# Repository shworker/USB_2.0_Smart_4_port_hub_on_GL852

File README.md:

# USB 2.0 Smart 4 port hub based on GL852
Not tested.
KiCAD 6 project + Screenshot with 3D View of PCB

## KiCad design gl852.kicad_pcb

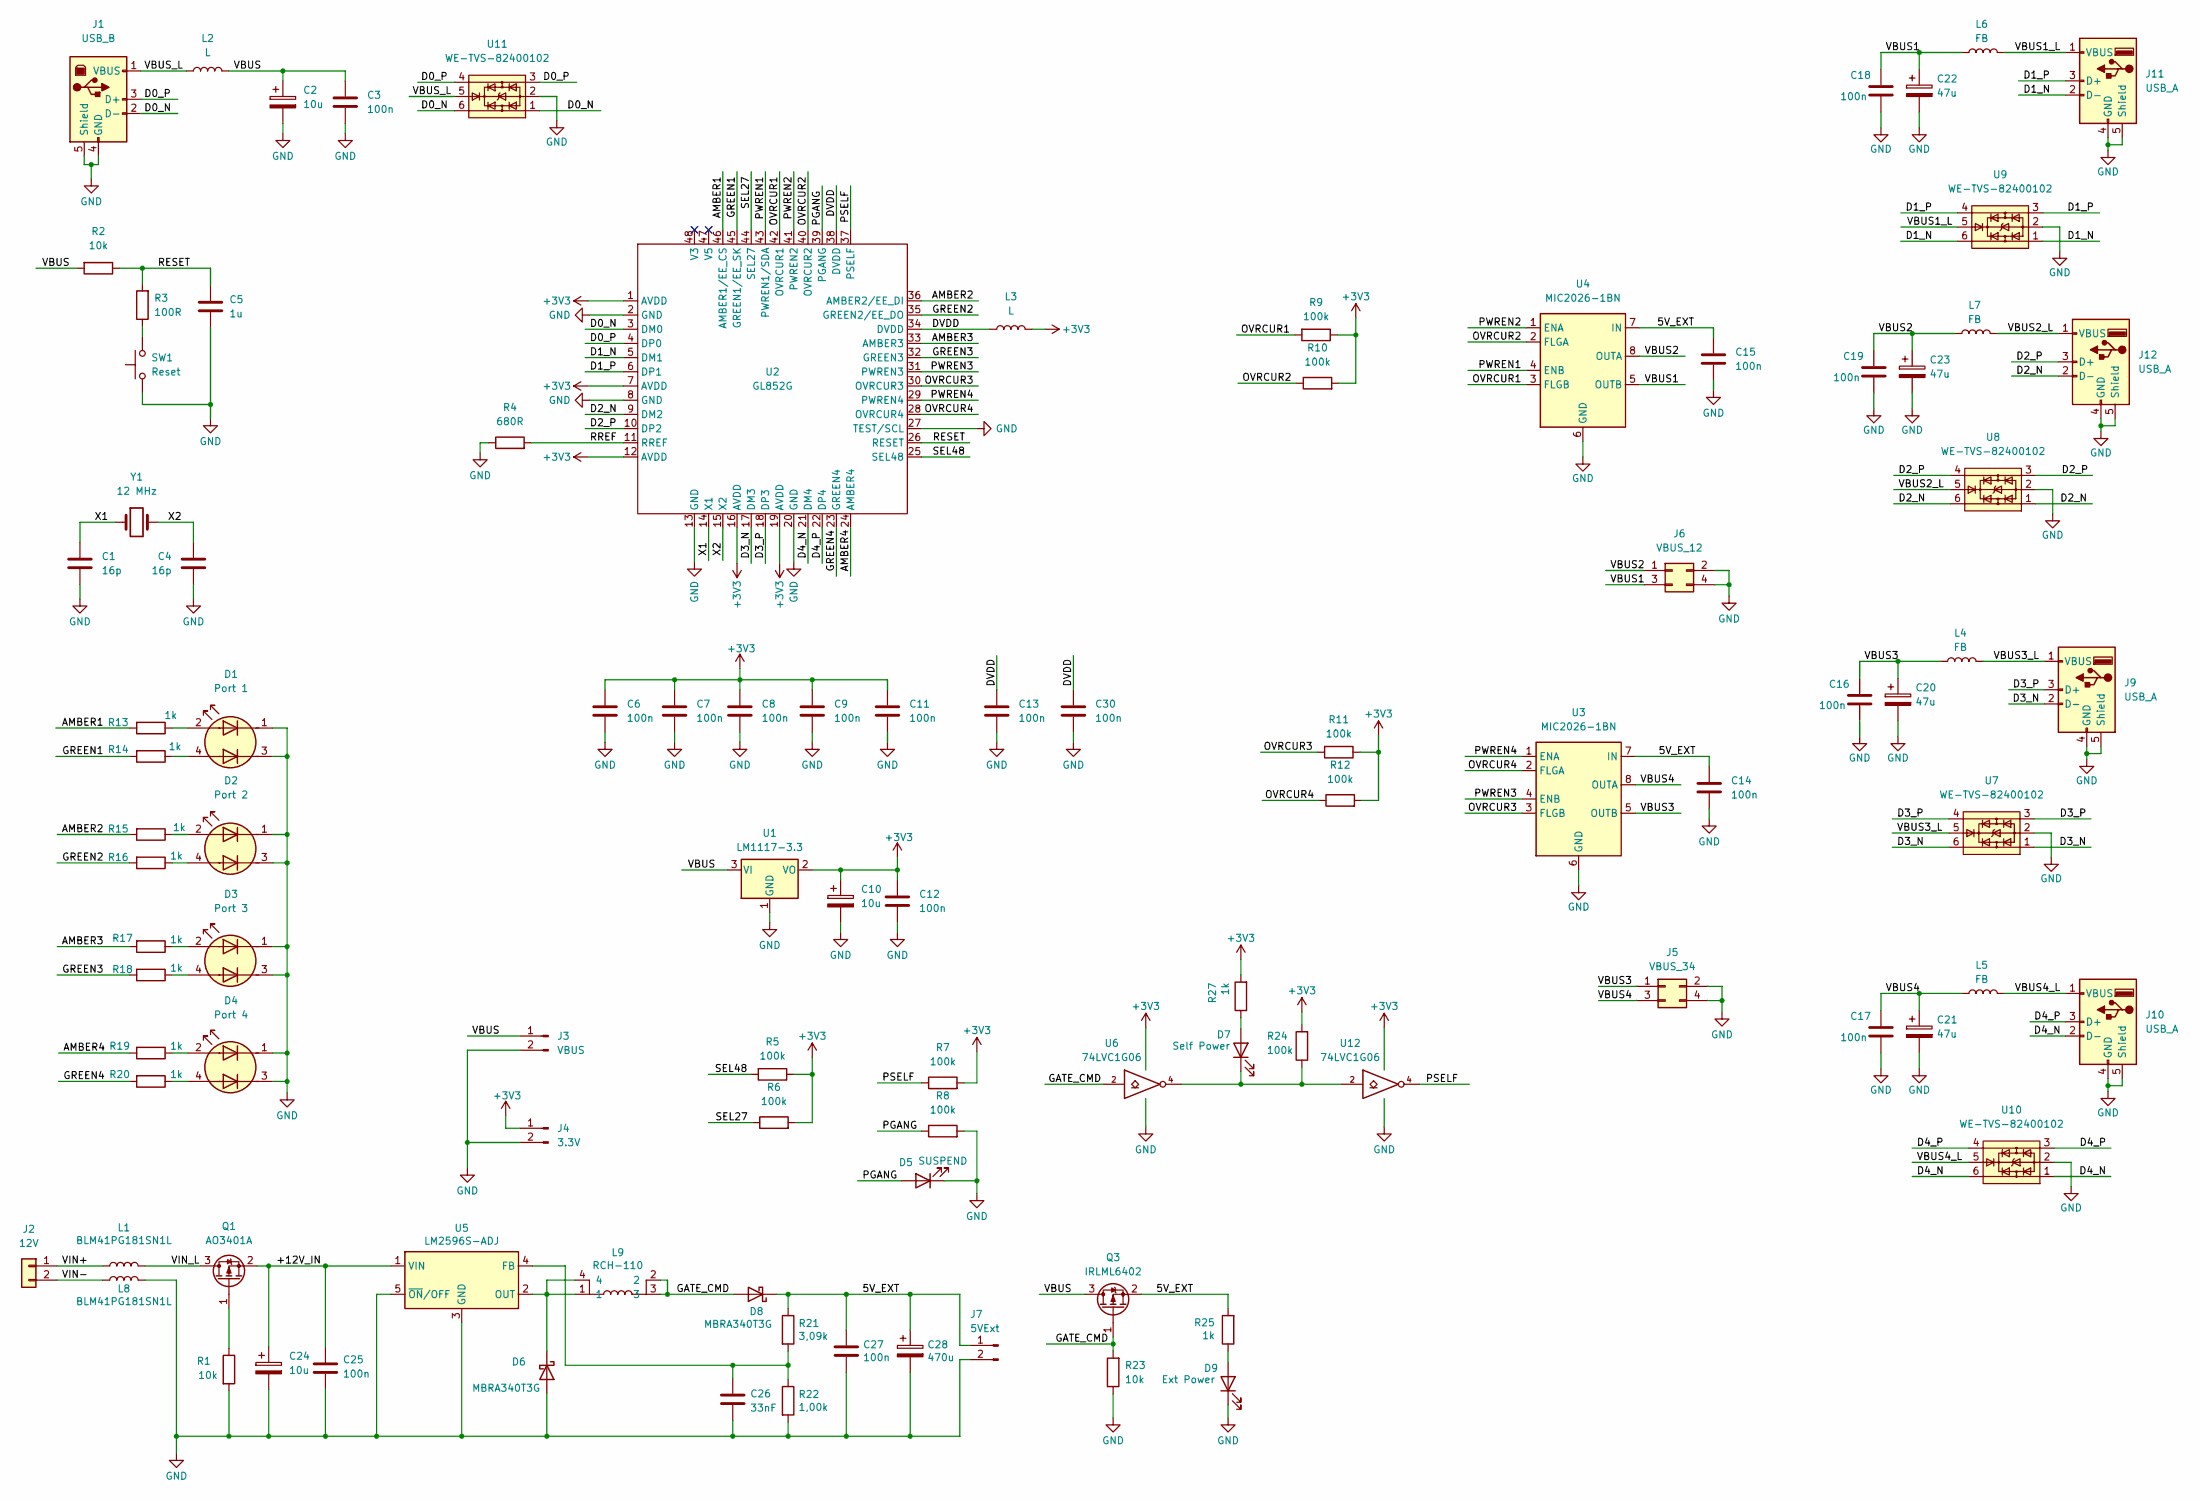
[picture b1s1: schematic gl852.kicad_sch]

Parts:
C1, C4: 16p; C_0603_1608Metric_Pad1.08x0.95mm_HandSolder
C2: 10u; CP_EIA-3528-21_Kemet-B_Pad1.50x2.35mm_HandSolder
C3, C6, C7, C8, C9, C11, C12, C13, C14, C15, C16, C17, C18, C19, C25, C27, C30: 100n; C_0603_1608Metric_Pad1.08x0.95mm_HandSolder
C5: 1u; C_0603_1608Metric_Pad1.08x0.95mm_HandSolder
C10: 10u; CP_Radial_D5.0mm_P2.50mm
C20, C21, C22, C23: 47u; C_Radial_D6.3mm_H5.0mm_P2.50mm
C24: 10u; CP_Radial_D10.0mm_P5.00mm
C26: 33nF; C_0603_1608Metric_Pad1.08x0.95mm_HandSolder
C28: 470u; CP_Radial_D8.0mm_P3.50mm
D1: Port 1; LED_Kingbright_AAA3528ESGCT
D2: Port 2; LED_Kingbright_AAA3528ESGCT
D3: Port 3; LED_Kingbright_AAA3528ESGCT
D4: Port 4; LED_Kingbright_AAA3528ESGCT
D5: SUSPEND; LED_0805_2012Metric_Pad1.15x1.40mm_HandSolder
D6, D8: MBRA340T3G; D_SMC_Handsoldering
D7: Self Power; LED_0805_2012Metric_Pad1.15x1.40mm_HandSolder
D9: Ext Power; LED_0805_2012Metric_Pad1.15x1.40mm_HandSolder
J1: USB_B; USB_B_OST_USB-B1HSxx_Horizontal
J2: 12V; PinHeader_1x02_P2.54mm_Vertical
J3: VBUS; PinHeader_1x02_P2.54mm_Vertical
J4: 3.3V; PinHeader_1x02_P2.54mm_Vertical
J5: VBUS_34; PinHeader_2x02_P2.54mm_Vertical
J6: VBUS_12; PinHeader_2x02_P2.54mm_Vertical
J7: 5VExt; PinHeader_1x02_P2.54mm_Vertical
J9, J10, J11, J12: USB_A; USB_A_CONNFLY_DS1095-WNR0
L1, L8: BLM41PG181SN1L; L_1806_4516Metric_Pad1.45x1.90mm_HandSolder
L2, L3: L; L_0805_2012Metric_Pad1.15x1.40mm_HandSolder
L4, L5, L6, L7: FB; L_0603_1608Metric_Pad1.05x0.95mm_HandSolder
L9: RCH-110; RCH110
Q1: AO3401A; SOT-23_Handsoldering
Q3: IRLML6402; SOT-23_Handsoldering
R1, R2, R23: 10k; R_0603_1608Metric_Pad0.98x0.95mm_HandSolder
R3: 100R; R_0603_1608Metric_Pad0.98x0.95mm_HandSolder
R4: 680R; R_0603_1608Metric_Pad0.98x0.95mm_HandSolder
R5, R6, R7, R8, R9, R10, R11, R12, R24: 100k; R_0603_1608Metric_Pad0.98x0.95mm_HandSolder
R13, R14, R15, R16, R17, R18, R19, R20, R25, R27: 1k; R_0603_1608Metric_Pad0.98x0.95mm_HandSolder
R21: 3,09k; R_0603_1608Metric_Pad0.98x0.95mm_HandSolder
R22: 1,00k; R_0603_1608Metric_Pad0.98x0.95mm_HandSolder
SW1: Reset; SW_Push_1P1T_NO_6x6mm_H9.5mm
U1: LM1117-3.3; SOT-223-3_TabPin2
U2: GL852G; LQFP-48_7x7mm_P0.5mm
U3, U4: MIC2026-1BN; SOIC-8_3.9x4.9mm_P1.27mm
U5: LM2596S-ADJ; TO-263-5_TabPin3
U6, U12: 74LVC1G06; SOT-23-5_HandSoldering
U7, U8, U9, U10, U11: WE-TVS-82400102; SOT-23-6
Y1: 12 MHz; Crystal_HC49-4H_Vertical

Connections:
+3V3: C6.1, C7.1, C8.1, C9.1, C10.1, C11.1, C12.1, J4.1, L3.2, R5.1, R6.2, R7.2, R9.1, R10.2, R11.1, R12.2, R24.2, R27.2, U1.2 (VO), U2.1 (AVDD), U2.7 (AVDD), U2.12 (AVDD), U2.16 (AVDD), U2.19 (AVDD), U6.5 (VCC), U12.5 (VCC)
/5V_EXT: C14.1, C15.1, C27.1, C28.1, D8.1 (K), J7.1, Q3.2 (S), R21.1, R25.2, U3.7 (IN), U4.7 (IN)
/+12V_IN: C24.1, C25.1, Q1.2 (S), U5.1 (VIN)
/AMBER1: R13.2, U2.46 (AMBER1/EE_CS)
/AMBER2: R15.2, U2.36 (AMBER2/EE_DI)
/AMBER3: R17.2, U2.33 (AMBER3)
/AMBER4: R19.2, U2.24 (AMBER4)
/D0_N: J1.2 (D-), U2.3 (DM0), U11.1, U11.6
/D0_P: J1.3 (D+), U2.4 (DP0), U11.3, U11.4
/D1_N: J11.2 (D-), U2.5 (DM1), U9.1, U9.6
/D1_P: J11.3 (D+), U2.6 (DP1), U9.3, U9.4
/D2_N: J12.2 (D-), U2.9 (DM2), U8.1, U8.6
/D2_P: J12.3 (D+), U2.10 (DP2), U8.3, U8.4
/D3_N: J9.2 (D-), U2.17 (DM3), U7.1, U7.6
/D3_P: J9.3 (D+), U2.18 (DP3), U7.3, U7.4
/D4_N: J10.2 (D-), U2.21 (DM4), U10.1, U10.6
/D4_P: J10.3 (D+), U2.22 (DP4), U10.3, U10.4
/DVDD: C13.1, C30.1, L3.1, U2.34 (DVDD), U2.38 (DVDD)
/GATE_CMD: D8.2 (A), L9.2, L9.3, Q3.1 (G), R23.2, U6.2
/GREEN1: R14.2, U2.45 (GREEN1/EE_SK)
/GREEN2: R16.2, U2.35 (GREEN2/EE_DO)
/GREEN3: R18.2, U2.32 (GREEN3)
/GREEN4: R20.2, U2.23 (GREEN4)
/OVRCUR1: R9.2, U2.42 (OVRCUR1), U4.3 (FLGB)
/OVRCUR2: R10.1, U2.40 (OVRCUR2), U4.2 (FLGA)
/OVRCUR3: R11.2, U2.30 (OVRCUR3), U3.3 (FLGB)
/OVRCUR4: R12.1, U2.28 (OVRCUR4), U3.2 (FLGA)
/PGANG: D5.2 (A), R8.1, U2.39 (PGANG)
/PSELF: R7.1, U2.37 (PSELF), U12.4
/PWREN1: U2.43 (PWREN1/SDA), U4.4 (ENB)
/PWREN2: U2.41 (PWREN2), U4.1 (ENA)
/PWREN3: U2.31 (PWREN3), U3.4 (ENB)
/PWREN4: U2.29 (PWREN4), U3.1 (ENA)
/RESET: C5.1, R2.1, R3.2, U2.26 (RESET)
/RREF: R4.2, U2.11 (RREF)
/SEL27: R6.1, U2.44 (SEL27)
/SEL48: R5.2, U2.25 (SEL48)
/VBUS: C2.1, C3.1, J3.1, L2.2, Q3.3 (D), R2.2, U1.3 (VI)
/VBUS1: C18.1, C22.1, J6.3, L6.1, U4.5 (OUTB)
/VBUS1_L: J11.1 (VBUS), L6.2, U9.5
/VBUS2: C19.1, C23.1, J6.1, L7.1, U4.8 (OUTA)
/VBUS2_L: J12.1 (VBUS), L7.2, U8.5
/VBUS3: C16.1, C20.1, J5.1, L4.1, U3.5 (OUTB)
/VBUS3_L: J9.1 (VBUS), L4.2, U7.5
/VBUS4: C17.1, C21.1, J5.3, L5.1, U3.8 (OUTA)
/VBUS4_L: J10.1 (VBUS), L5.2, U10.5
/VBUS_L: J1.1 (VBUS), L2.1, U11.5
/VIN+: J2.1, L1.1
/VIN-: J2.2, L8.1
/VIN_L: L1.2, Q1.3 (D)
/X1: C1.1, U2.14 (X1), Y1.1
/X2: C4.1, U2.15 (X2), Y1.2
GND: C1.2, C2.2, C3.2, C4.2, C5.2, C6.2, C7.2, C8.2, C9.2, C10.2, C11.2, C12.2, C13.2, C14.2, C15.2, C16.2, C17.2, C18.2, C19.2, C20.2, C21.2, C22.2, C23.2, C24.2, C25.2, C26.2, C27.2, C28.2, C30.2, D1.1 (A1), D1.3 (A2), D2.1 (A1), D2.3 (A2), D3.1 (A1), D3.3 (A2), D4.1 (A1), D4.3 (A2), D5.1 (K), D6.2 (A), D9.1 (K), J1.4 (GND), J1.5 (Shield), J3.2, J4.2, J5.2, J5.4, J6.2, J6.4, J7.2, J9.4 (GND), J9.5 (Shield), J10.4 (GND), J10.5 (Shield), J11.4 (GND), J11.5 (Shield), J12.4 (GND), J12.5 (Shield), L8.2, R1.2, R4.1, R8.2, R22.2, R23.1, SW1.1, U1.1 (GND), U2.2 (GND), U2.8 (GND), U2.13 (GND), U2.20 (GND), U2.27 (TEST/SCL), U3.6 (GND), U4.6 (GND), U5.3 (GND), U5.5 (~ON/OFF), U6.3 (GND), U7.2, U8.2, U9.2, U10.2, U11.2, U12.3 (GND)
unnamed: C26.1, R21.2, R22.1, U5.4 (FB)
unnamed: D1.2 (K1), R13.1
unnamed: D1.4 (K2), R14.1
unnamed: D2.2 (K1), R15.1
unnamed: D2.4 (K2), R16.1
unnamed: D3.2 (K1), R17.1
unnamed: D3.4 (K2), R18.1
unnamed: D4.2 (K1), R19.1
unnamed: D4.4 (K2), R20.1
unnamed: D6.1 (K), L9.1, L9.4, U5.2 (OUT)
unnamed: D7.1 (K), R24.1, U6.4, U12.2
unnamed: D7.2 (A), R27.1
unnamed: D9.2 (A), R25.1
unnamed: Q1.1 (G), R1.1
unnamed: R3.1, SW1.2

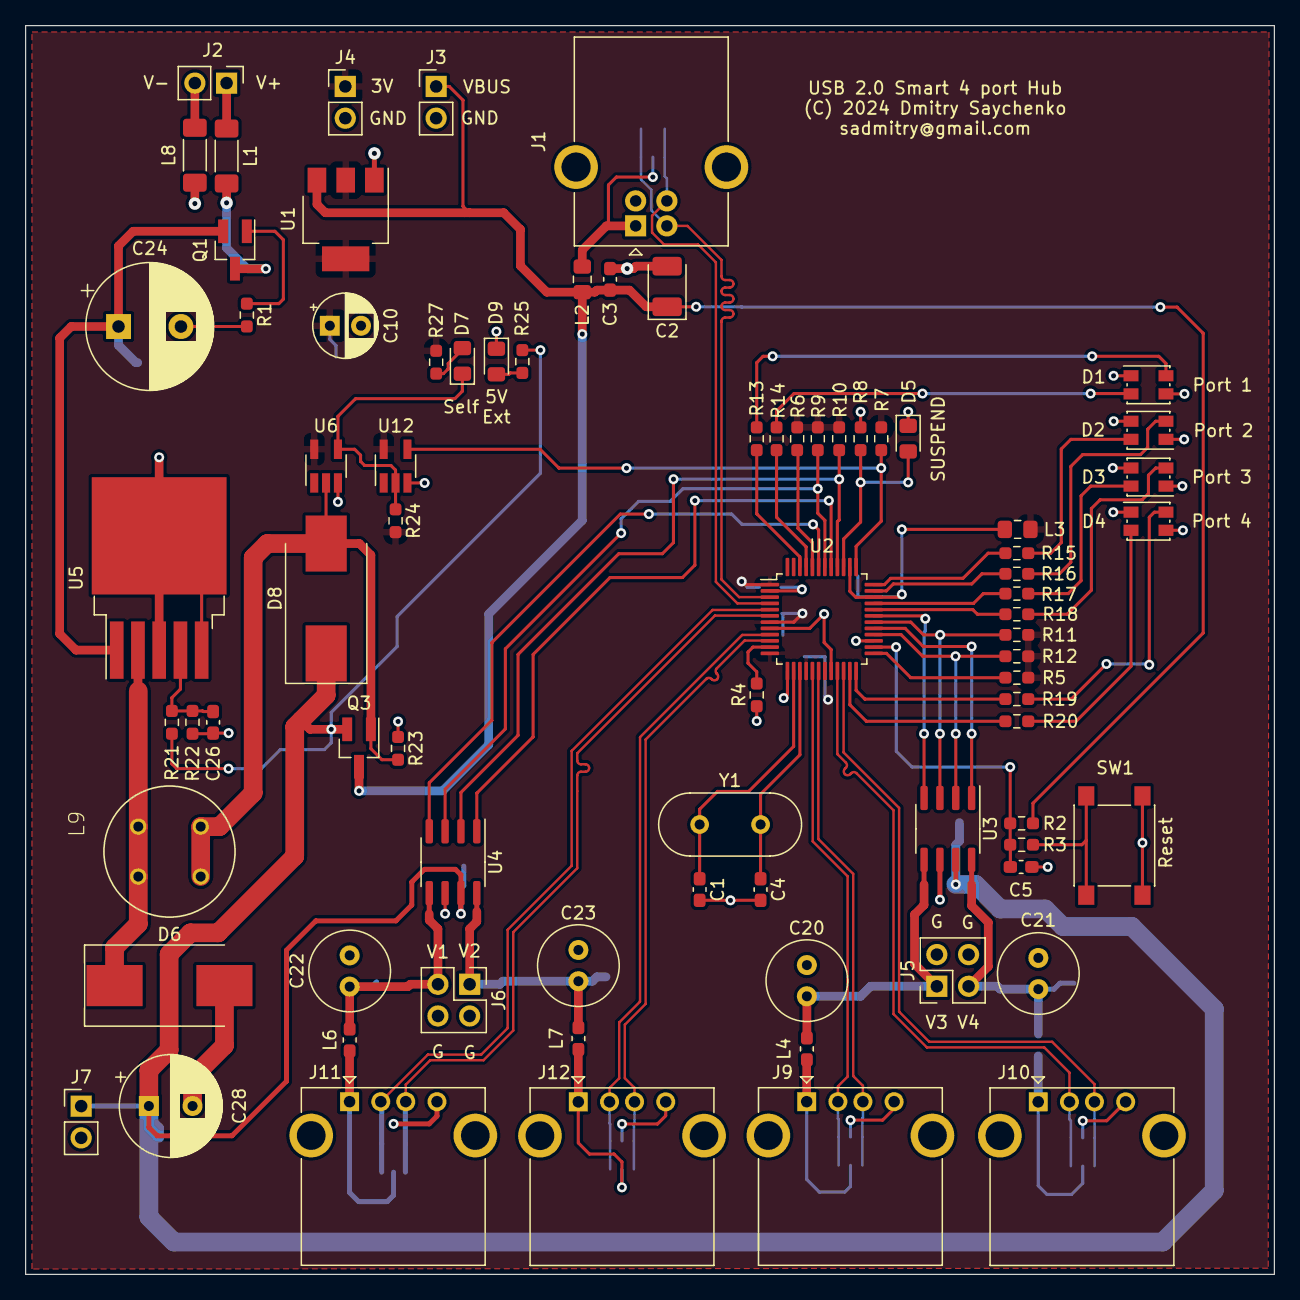
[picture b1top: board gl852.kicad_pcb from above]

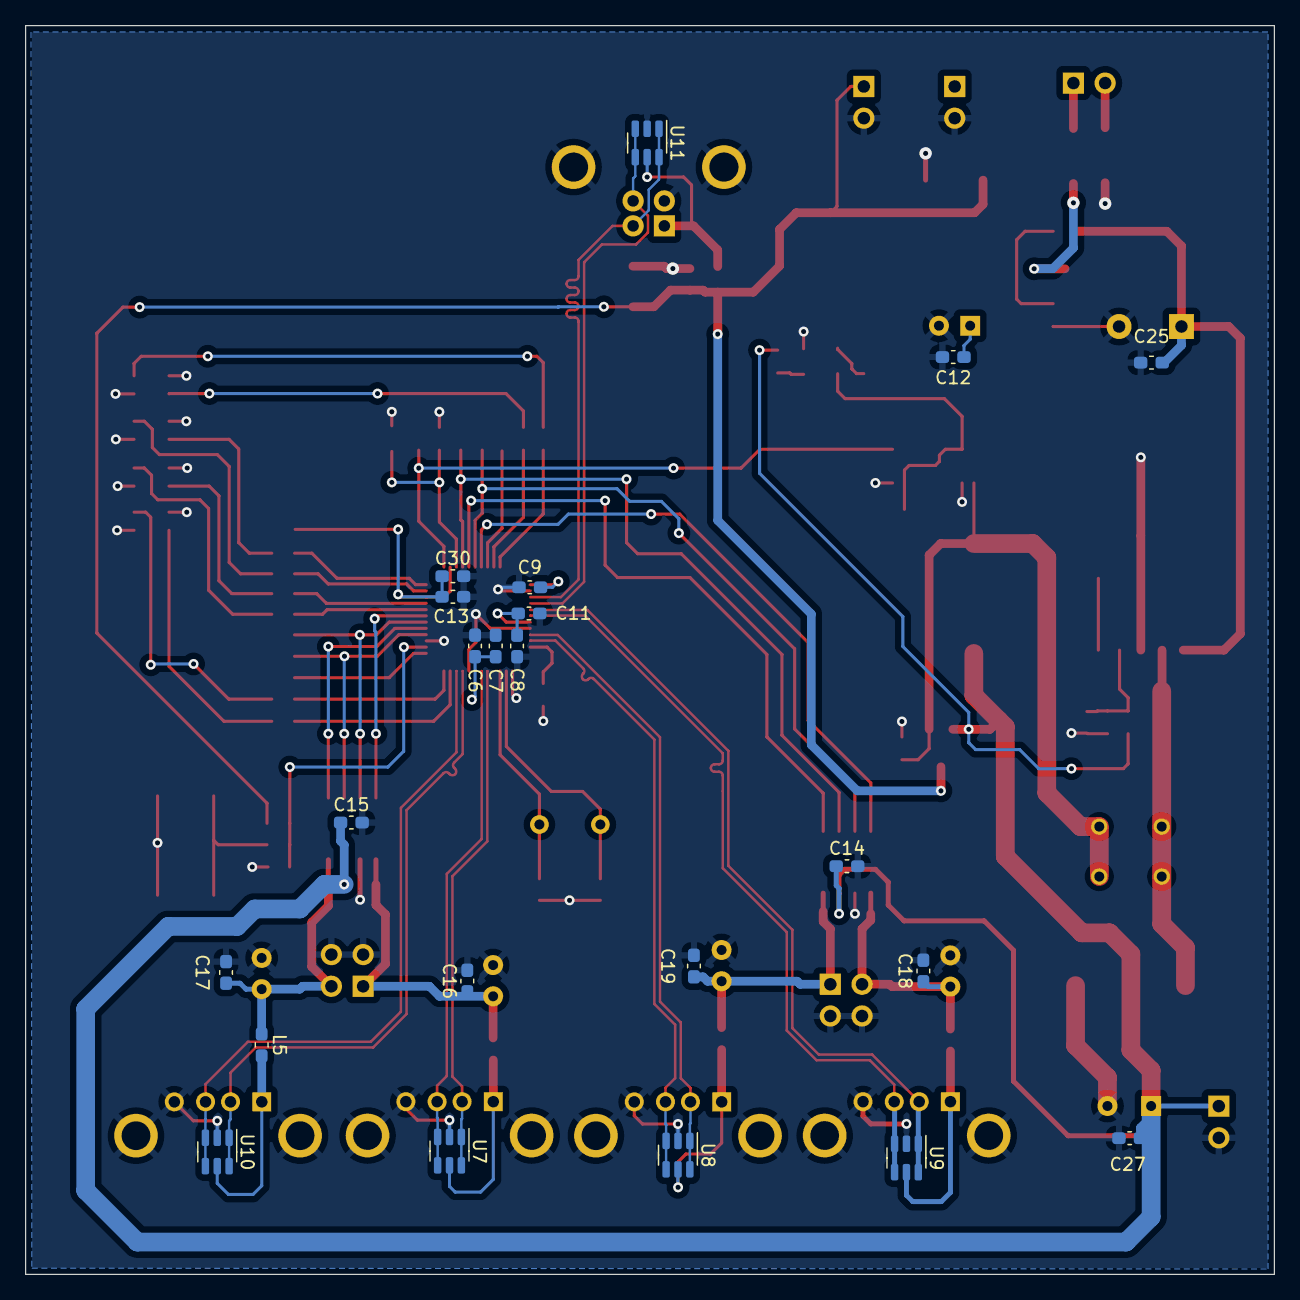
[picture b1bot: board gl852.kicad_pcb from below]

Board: 2 copper layers, 100.0 x 100.0 mm, 100 parts (22 on the bottom side), 68 nets.

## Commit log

2024-06-27 Modified power section

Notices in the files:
gl852.kicad_pcb:
(C) 2024 Dmitry Saychenko
